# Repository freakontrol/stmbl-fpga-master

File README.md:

DISCLAIMER
===

THE AUTHORS OF THIS SOFTWARE ACCEPT ABSOLUTELY NO LIABILITY FOR
ANY HARM OR LOSS RESULTING FROM ITS USE.  IT IS _EXTREMELY_ UNWISE
TO RELY ON SOFTWARE ALONE FOR SAFETY.  Any machinery capable of
harming persons must have provisions for completely removing power
from all motors, etc, before persons enter any danger area.  All
machinery must be designed to comply with local and national safety
codes, and the authors of this software can not, and do not, take
any responsibility for such compliance.

This firmware in the folder hostmot2-firmware originates from Mesa Electronics.
This repository  is released under the GPLv3.

STMBL FPGA Master
=====

This is a FPGA controller board specifically designed to be used as a master for up to 12 stmbl drives. It can be used for other applications.
The hardware has the same form factor as the [STMBL](https://github.com/freakontrol/stmbl) v5 drives.
The FPGA runs the hostmot2 firmware.

## Hardware overview
- 12 SSerial ports
- 2 SSerial/RS485 ports
- one 26 Pin parallel expansion port (17 IOs)
- one 24V Input
- one 24V Output
- Host connection via Ethernet or SPI (if used with a RPi 4 or 5)
- 24V Power Input (provides also power to the Raspberry Pi)

## Known Bugs

**Please note that the hardware and firmware are in an early prototyping stage.**
Don't manufacture the version 0.9 because of the reversed SSerial pinouts

- affects hardware v0.9: Pinout of SSerial 0-5 and 12-13 is reversed (1-8, 2-7, ...), use a [Rollover cable](https://en.wikipedia.org/wiki/Rollover_cable)
- SSerial 13 ist not working, there seems to be a bug in the PIN file
- At the moment there is no option to enable power to the SSerial ports before loading the hm2 driver. So it is not possible to use SSerial devices that a powered form the SSerial connector. Can be fixed in firmware.

* * * 
If you have questions about this project contact me [here](https://matrix.to/#/@jst:freiburg.social).

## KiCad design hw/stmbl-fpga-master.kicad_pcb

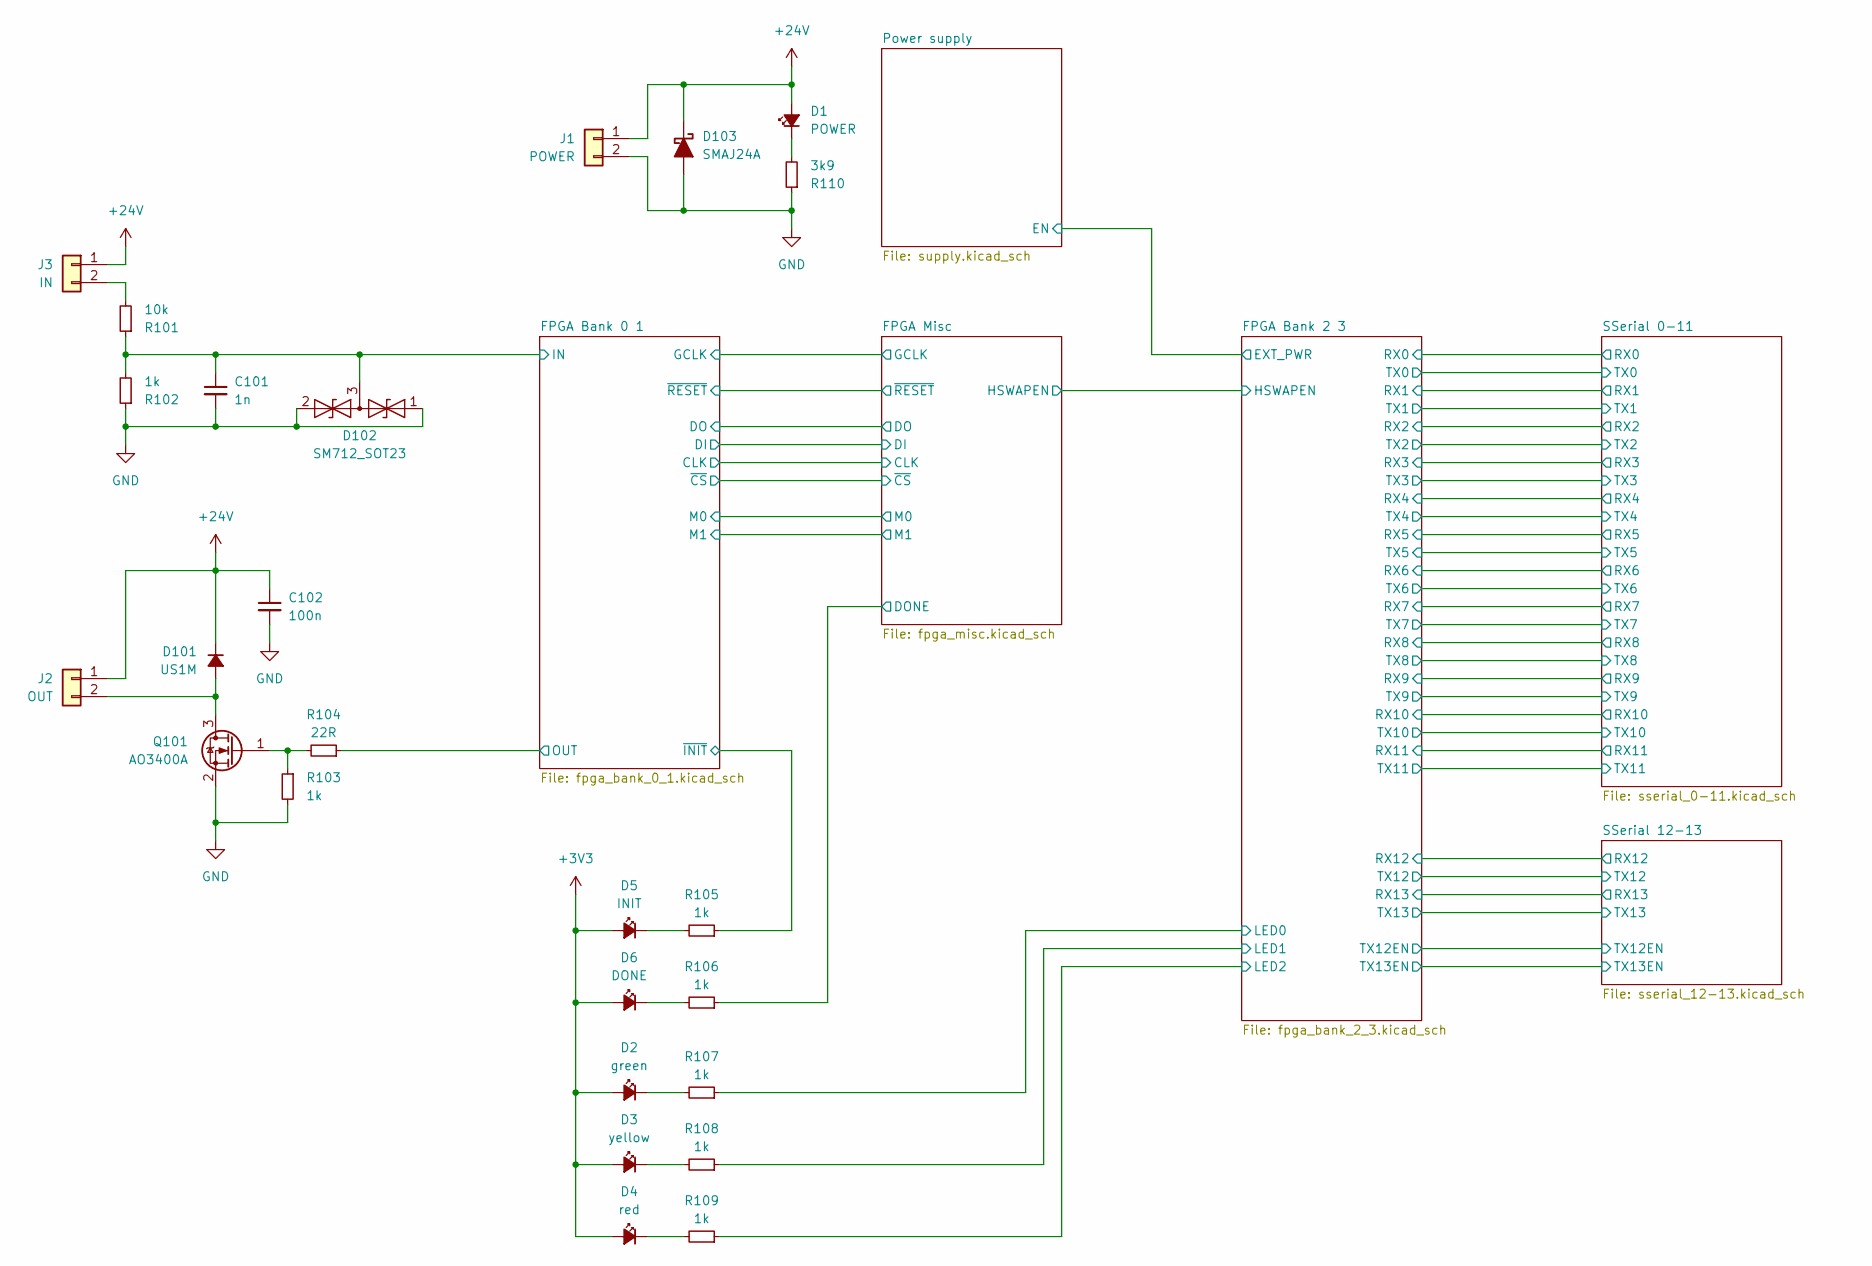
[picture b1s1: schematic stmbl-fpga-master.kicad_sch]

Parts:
C101: 1n; C_0603_1608Metric
C102: 100n; C_0603_1608Metric
D1: POWER; LED-0805-SIDE
D2: green; LED-0805-SIDE
D3: yellow; LED-0805-SIDE
D4: red; LED-0805-SIDE
D5: INIT; LED_0603_1608Metric
D6: DONE; LED_0603_1608Metric
D101: US1M; D_SMA
D102: SM712_SOT23; SOT-23
D103: SMAJ24A; D_SMA
J1: POWER; PhoenixContact_MC_1,5_2-G-3.5_1x02_P3.50mm_Horizontal
J2: OUT; PhoenixContact_MC_1,5_2-G-3.5_1x02_P3.50mm_Horizontal
J3: IN; PhoenixContact_MC_1,5_2-G-3.5_1x02_P3.50mm_Horizontal
Q101: AO3400A; SOT-23
R101: 10k; R_0603_1608Metric
R102, R103, R105, R106, R107, R108, R109: 1k; R_0603_1608Metric
R104: 22R; R_0603_1608Metric
R110: 3k9; R_0603_1608Metric

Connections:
+3V3: D2.2 (A), D3.2 (A), D4.2 (A), D5.2 (A), D6.2 (A); also elsewhere on the board
+24V: C102.1, D1.2 (A), D101.1 (K), D103.1 (K), J1.1, J2.1, J3.1; also elsewhere on the board
/FPGA Bank 0 1/IN: C101.1, D102.3 (common), R101.1, R102.2; also elsewhere on the board
/FPGA Bank 0 1/OUT: R104.1; also elsewhere on the board
/FPGA Bank 0 1/~INIT: R105.1; also elsewhere on the board
/FPGA Bank 2 3/LED0: R107.1; also elsewhere on the board
/FPGA Bank 2 3/LED1: R108.1; also elsewhere on the board
/FPGA Bank 2 3/LED2: R109.1; also elsewhere on the board
/FPGA Misc/DONE: R106.1; also elsewhere on the board
GND: C101.2, C102.2, D102.1 (A1), D102.2 (A2), D103.2 (A), J1.2, Q101.2 (S), R102.1, R103.2, R110.1; also elsewhere on the board
unnamed: D1.1 (K), R110.2
unnamed: D2.1 (K), R107.2
unnamed: D3.1 (K), R108.2
unnamed: D4.1 (K), R109.2
unnamed: D5.1 (K), R105.2
unnamed: D6.1 (K), R106.2
unnamed: D101.2 (A), J2.2, Q101.3 (D)
unnamed: J3.2, R101.2
unnamed: Q101.1 (G), R103.1, R104.2

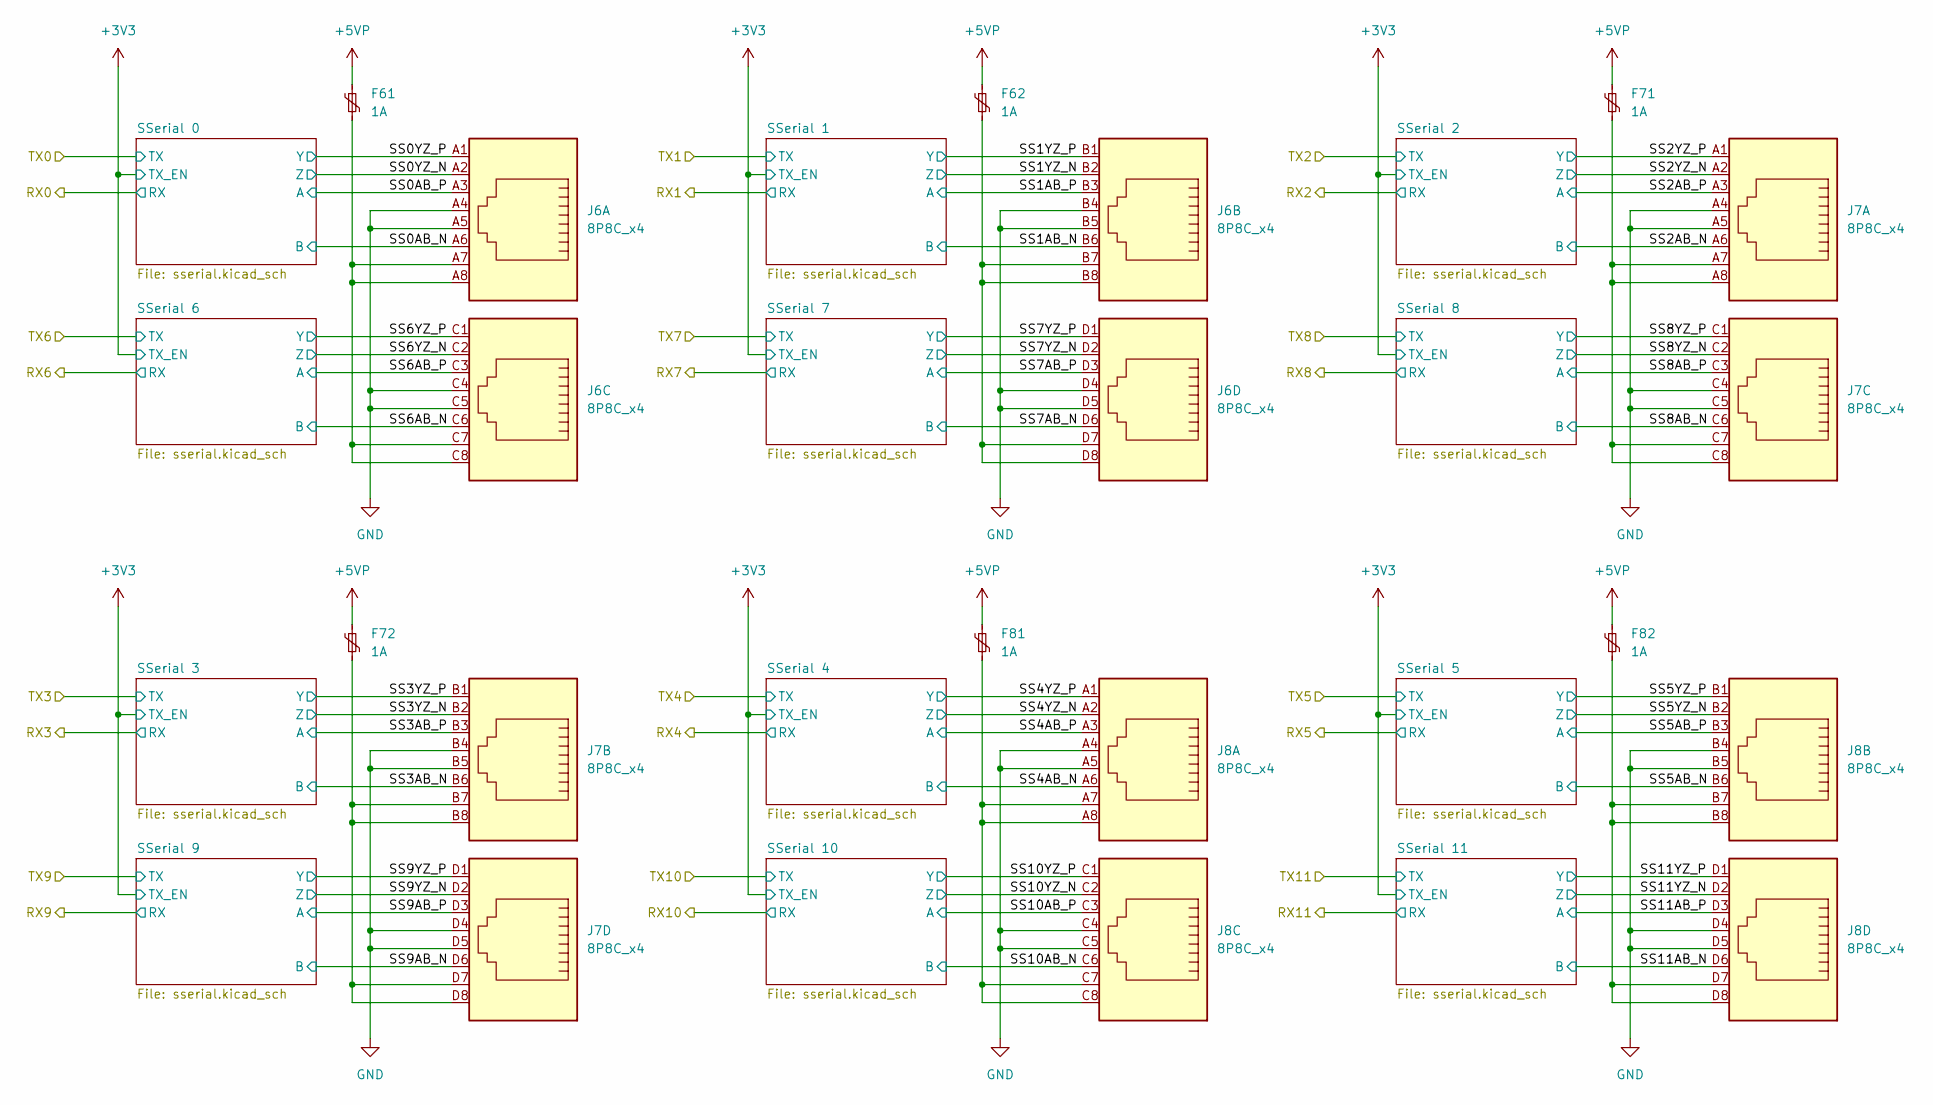
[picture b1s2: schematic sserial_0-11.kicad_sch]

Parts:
F61, F62, F71, F72, F81, F82: 1A; Fuse_1206_3216Metric
J6, J7, J8: 8P8C_x4; MJ5988-B022-HPRN1

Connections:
+5VP: F61.1, F62.1, F71.1, F72.1, F81.1, F82.1; also elsewhere on the board
/SSerial 0-11/SS0AB_N: J6.A6; also elsewhere on the board
/SSerial 0-11/SS0AB_P: J6.A3; also elsewhere on the board
/SSerial 0-11/SS0YZ_N: J6.A2; also elsewhere on the board
/SSerial 0-11/SS0YZ_P: J6.A1; also elsewhere on the board
/SSerial 0-11/SS1AB_N: J6.B6; also elsewhere on the board
/SSerial 0-11/SS1AB_P: J6.B3; also elsewhere on the board
/SSerial 0-11/SS1YZ_N: J6.B2; also elsewhere on the board
/SSerial 0-11/SS1YZ_P: J6.B1; also elsewhere on the board
/SSerial 0-11/SS2AB_N: J7.A6; also elsewhere on the board
/SSerial 0-11/SS2AB_P: J7.A3; also elsewhere on the board
/SSerial 0-11/SS2YZ_N: J7.A2; also elsewhere on the board
/SSerial 0-11/SS2YZ_P: J7.A1; also elsewhere on the board
/SSerial 0-11/SS3AB_N: J7.B6; also elsewhere on the board
/SSerial 0-11/SS3AB_P: J7.B3; also elsewhere on the board
/SSerial 0-11/SS3YZ_N: J7.B2; also elsewhere on the board
/SSerial 0-11/SS3YZ_P: J7.B1; also elsewhere on the board
/SSerial 0-11/SS4AB_N: J8.A6; also elsewhere on the board
/SSerial 0-11/SS4AB_P: J8.A3; also elsewhere on the board
/SSerial 0-11/SS4YZ_N: J8.A2; also elsewhere on the board
/SSerial 0-11/SS4YZ_P: J8.A1; also elsewhere on the board
/SSerial 0-11/SS5AB_N: J8.B6; also elsewhere on the board
/SSerial 0-11/SS5AB_P: J8.B3; also elsewhere on the board
/SSerial 0-11/SS5YZ_N: J8.B2; also elsewhere on the board
/SSerial 0-11/SS5YZ_P: J8.B1; also elsewhere on the board
/SSerial 0-11/SS6AB_N: J6.C6; also elsewhere on the board
/SSerial 0-11/SS6AB_P: J6.C3; also elsewhere on the board
/SSerial 0-11/SS6YZ_N: J6.C2; also elsewhere on the board
/SSerial 0-11/SS6YZ_P: J6.C1; also elsewhere on the board
/SSerial 0-11/SS7AB_N: J6.D6; also elsewhere on the board
/SSerial 0-11/SS7AB_P: J6.D3; also elsewhere on the board
/SSerial 0-11/SS7YZ_N: J6.D2; also elsewhere on the board
/SSerial 0-11/SS7YZ_P: J6.D1; also elsewhere on the board
/SSerial 0-11/SS8AB_N: J7.C6; also elsewhere on the board
/SSerial 0-11/SS8AB_P: J7.C3; also elsewhere on the board
/SSerial 0-11/SS8YZ_N: J7.C2; also elsewhere on the board
/SSerial 0-11/SS8YZ_P: J7.C1; also elsewhere on the board
/SSerial 0-11/SS9AB_N: J7.D6; also elsewhere on the board
/SSerial 0-11/SS9AB_P: J7.D3; also elsewhere on the board
/SSerial 0-11/SS9YZ_N: J7.D2; also elsewhere on the board
/SSerial 0-11/SS9YZ_P: J7.D1; also elsewhere on the board
/SSerial 0-11/SS10AB_N: J8.C6; also elsewhere on the board
/SSerial 0-11/SS10AB_P: J8.C3; also elsewhere on the board
/SSerial 0-11/SS10YZ_N: J8.C2; also elsewhere on the board
/SSerial 0-11/SS10YZ_P: J8.C1; also elsewhere on the board
/SSerial 0-11/SS11AB_N: J8.D6; also elsewhere on the board
/SSerial 0-11/SS11AB_P: J8.D3; also elsewhere on the board
/SSerial 0-11/SS11YZ_N: J8.D2; also elsewhere on the board
/SSerial 0-11/SS11YZ_P: J8.D1; also elsewhere on the board
GND: J6.A4, J6.A5, J6.B4, J6.B5, J6.C4, J6.C5, J6.D4, J6.D5, J7.A4, J7.A5, J7.B4, J7.B5, J7.C4, J7.C5, J7.D4, J7.D5, J8.A4, J8.A5, J8.B4, J8.B5, J8.C4, J8.C5, J8.D4, J8.D5; also elsewhere on the board
unnamed: F61.2, J6.A7, J6.A8, J6.C7, J6.C8
unnamed: F62.2, J6.B7, J6.B8, J6.D7, J6.D8
unnamed: F71.2, J7.A7, J7.A8, J7.C7, J7.C8
unnamed: F72.2, J7.B7, J7.B8, J7.D7, J7.D8
unnamed: F81.2, J8.A7, J8.A8, J8.C7, J8.C8
unnamed: F82.2, J8.B7, J8.B8, J8.D7, J8.D8

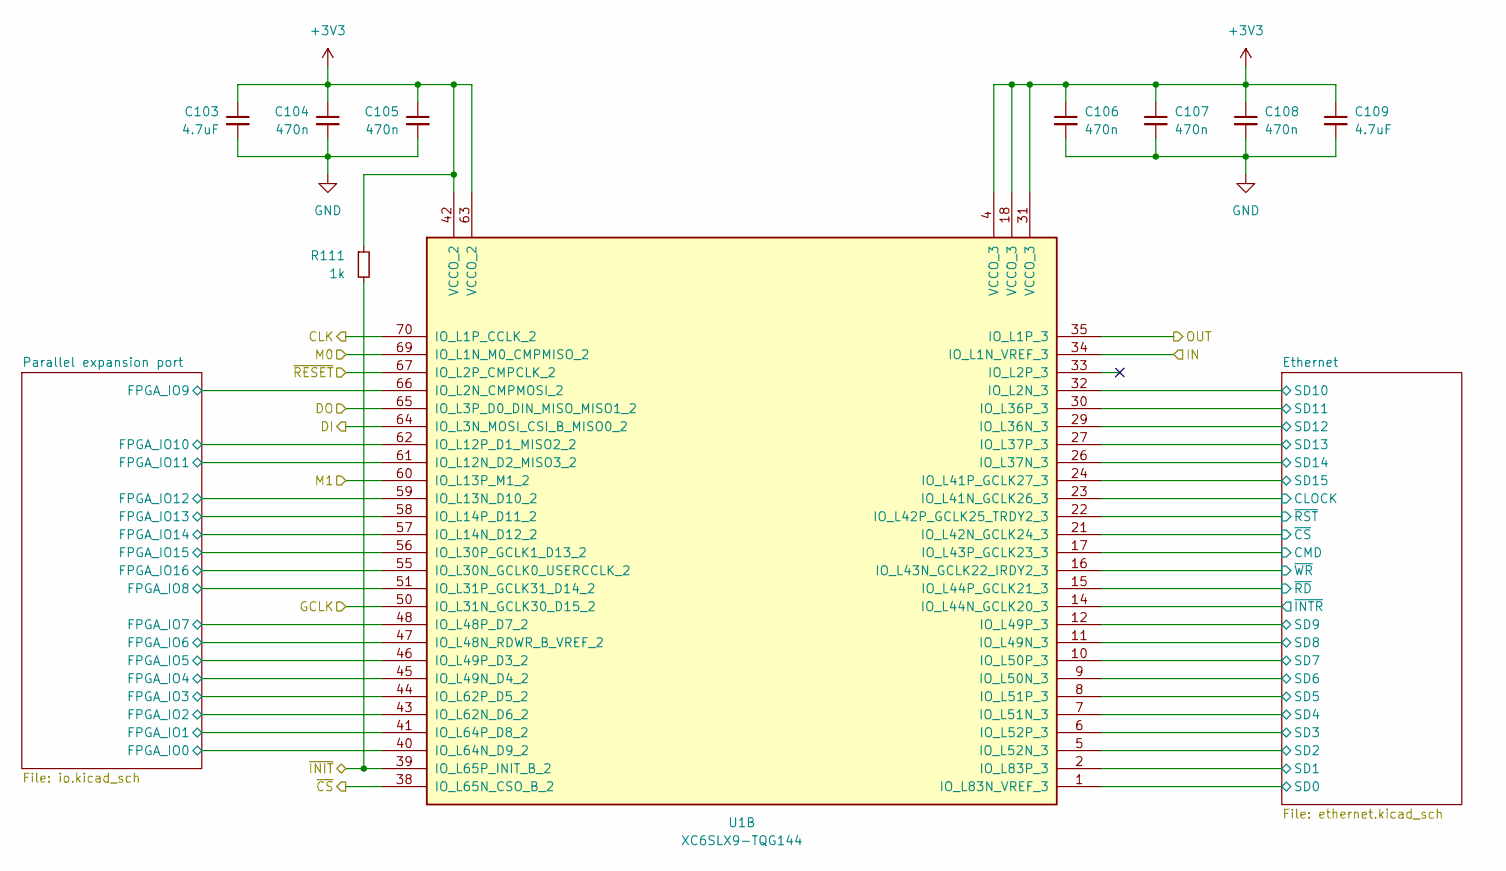
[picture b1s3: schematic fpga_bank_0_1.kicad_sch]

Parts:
C103, C109: 4.7uF; C_0603_1608Metric
C104, C105, C106, C107, C108: 470n; C_0603_1608Metric
R111: 1k; R_0603_1608Metric
U1: XC6SLX9-TQG144; TQFP-144_20x20mm_P0.5mm

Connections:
+3V3: C103.1, C104.1, C105.1, C106.1, C107.1, C108.1, C109.1, R111.1, U1.4 (VCCO_3), U1.18 (VCCO_3), U1.31 (VCCO_3), U1.42 (VCCO_2), U1.63 (VCCO_2); also elsewhere on the board
/FPGA Bank 0 1/CLK: U1.70 (IO_L1P_CCLK_2); also elsewhere on the board
/FPGA Bank 0 1/DI: U1.64 (IO_L3N_MOSI_CSI_B_MISO0_2); also elsewhere on the board
/FPGA Bank 0 1/DO: U1.65 (IO_L3P_D0_DIN_MISO_MISO1_2); also elsewhere on the board
/FPGA Bank 0 1/Ethernet/CLOCK: U1.23 (IO_L41N_GCLK26_3); also elsewhere on the board
/FPGA Bank 0 1/Ethernet/CMD: U1.17 (IO_L43P_GCLK23_3); also elsewhere on the board
/FPGA Bank 0 1/Ethernet/SD0: U1.1 (IO_L83N_VREF_3); also elsewhere on the board
/FPGA Bank 0 1/Ethernet/SD1: U1.2 (IO_L83P_3); also elsewhere on the board
/FPGA Bank 0 1/Ethernet/SD2: U1.5 (IO_L52N_3); also elsewhere on the board
/FPGA Bank 0 1/Ethernet/SD3: U1.6 (IO_L52P_3); also elsewhere on the board
/FPGA Bank 0 1/Ethernet/SD4: U1.7 (IO_L51N_3); also elsewhere on the board
/FPGA Bank 0 1/Ethernet/SD5: U1.8 (IO_L51P_3); also elsewhere on the board
/FPGA Bank 0 1/Ethernet/SD6: U1.9 (IO_L50N_3); also elsewhere on the board
/FPGA Bank 0 1/Ethernet/SD7: U1.10 (IO_L50P_3); also elsewhere on the board
/FPGA Bank 0 1/Ethernet/SD8: U1.11 (IO_L49N_3); also elsewhere on the board
/FPGA Bank 0 1/Ethernet/SD9: U1.12 (IO_L49P_3); also elsewhere on the board
/FPGA Bank 0 1/Ethernet/SD10: U1.32 (IO_L2N_3); also elsewhere on the board
/FPGA Bank 0 1/Ethernet/SD11: U1.30 (IO_L36P_3); also elsewhere on the board
/FPGA Bank 0 1/Ethernet/SD12: U1.29 (IO_L36N_3); also elsewhere on the board
/FPGA Bank 0 1/Ethernet/SD13: U1.27 (IO_L37P_3); also elsewhere on the board
/FPGA Bank 0 1/Ethernet/SD14: U1.26 (IO_L37N_3); also elsewhere on the board
/FPGA Bank 0 1/Ethernet/SD15: U1.24 (IO_L41P_GCLK27_3); also elsewhere on the board
/FPGA Bank 0 1/Ethernet/~CS: U1.21 (IO_L42N_GCLK24_3); also elsewhere on the board
/FPGA Bank 0 1/Ethernet/~INTR: U1.14 (IO_L44N_GCLK20_3); also elsewhere on the board
/FPGA Bank 0 1/Ethernet/~RD: U1.15 (IO_L44P_GCLK21_3); also elsewhere on the board
/FPGA Bank 0 1/Ethernet/~RST: U1.22 (IO_L42P_GCLK25_TRDY2_3); also elsewhere on the board
/FPGA Bank 0 1/Ethernet/~WR: U1.16 (IO_L43N_GCLK22_IRDY2_3); also elsewhere on the board
/FPGA Bank 0 1/GCLK: U1.50 (IO_L31N_GCLK30_D15_2); also elsewhere on the board
/FPGA Bank 0 1/IN: U1.34 (IO_L1N_VREF_3); also elsewhere on the board
/FPGA Bank 0 1/M0: U1.69 (IO_L1N_M0_CMPMISO_2); also elsewhere on the board
/FPGA Bank 0 1/M1: U1.60 (IO_L13P_M1_2); also elsewhere on the board
/FPGA Bank 0 1/OUT: U1.35 (IO_L1P_3); also elsewhere on the board
/FPGA Bank 0 1/Parallel expansion port/FPGA_IO0: U1.40 (IO_L64N_D9_2); also elsewhere on the board
/FPGA Bank 0 1/Parallel expansion port/FPGA_IO1: U1.41 (IO_L64P_D8_2); also elsewhere on the board
/FPGA Bank 0 1/Parallel expansion port/FPGA_IO2: U1.43 (IO_L62N_D6_2); also elsewhere on the board
/FPGA Bank 0 1/Parallel expansion port/FPGA_IO3: U1.44 (IO_L62P_D5_2); also elsewhere on the board
/FPGA Bank 0 1/Parallel expansion port/FPGA_IO4: U1.45 (IO_L49N_D4_2); also elsewhere on the board
/FPGA Bank 0 1/Parallel expansion port/FPGA_IO5: U1.46 (IO_L49P_D3_2); also elsewhere on the board
/FPGA Bank 0 1/Parallel expansion port/FPGA_IO6: U1.47 (IO_L48N_RDWR_B_VREF_2); also elsewhere on the board
/FPGA Bank 0 1/Parallel expansion port/FPGA_IO7: U1.48 (IO_L48P_D7_2); also elsewhere on the board
/FPGA Bank 0 1/Parallel expansion port/FPGA_IO8: U1.51 (IO_L31P_GCLK31_D14_2); also elsewhere on the board
/FPGA Bank 0 1/Parallel expansion port/FPGA_IO9: U1.66 (IO_L2N_CMPMOSI_2); also elsewhere on the board
/FPGA Bank 0 1/Parallel expansion port/FPGA_IO10: U1.62 (IO_L12P_D1_MISO2_2); also elsewhere on the board
/FPGA Bank 0 1/Parallel expansion port/FPGA_IO11: U1.61 (IO_L12N_D2_MISO3_2); also elsewhere on the board
/FPGA Bank 0 1/Parallel expansion port/FPGA_IO12: U1.59 (IO_L13N_D10_2); also elsewhere on the board
/FPGA Bank 0 1/Parallel expansion port/FPGA_IO13: U1.58 (IO_L14P_D11_2); also elsewhere on the board
/FPGA Bank 0 1/Parallel expansion port/FPGA_IO14: U1.57 (IO_L14N_D12_2); also elsewhere on the board
/FPGA Bank 0 1/Parallel expansion port/FPGA_IO15: U1.56 (IO_L30P_GCLK1_D13_2); also elsewhere on the board
/FPGA Bank 0 1/Parallel expansion port/FPGA_IO16: U1.55 (IO_L30N_GCLK0_USERCCLK_2); also elsewhere on the board
/FPGA Bank 0 1/~CS: U1.38 (IO_L65N_CSO_B_2); also elsewhere on the board
/FPGA Bank 0 1/~INIT: R111.2, U1.39 (IO_L65P_INIT_B_2); also elsewhere on the board
/FPGA Bank 0 1/~RESET: U1.67 (IO_L2P_CMPCLK_2); also elsewhere on the board
GND: C103.2, C104.2, C105.2, C106.2, C107.2, C108.2, C109.2; also elsewhere on the board

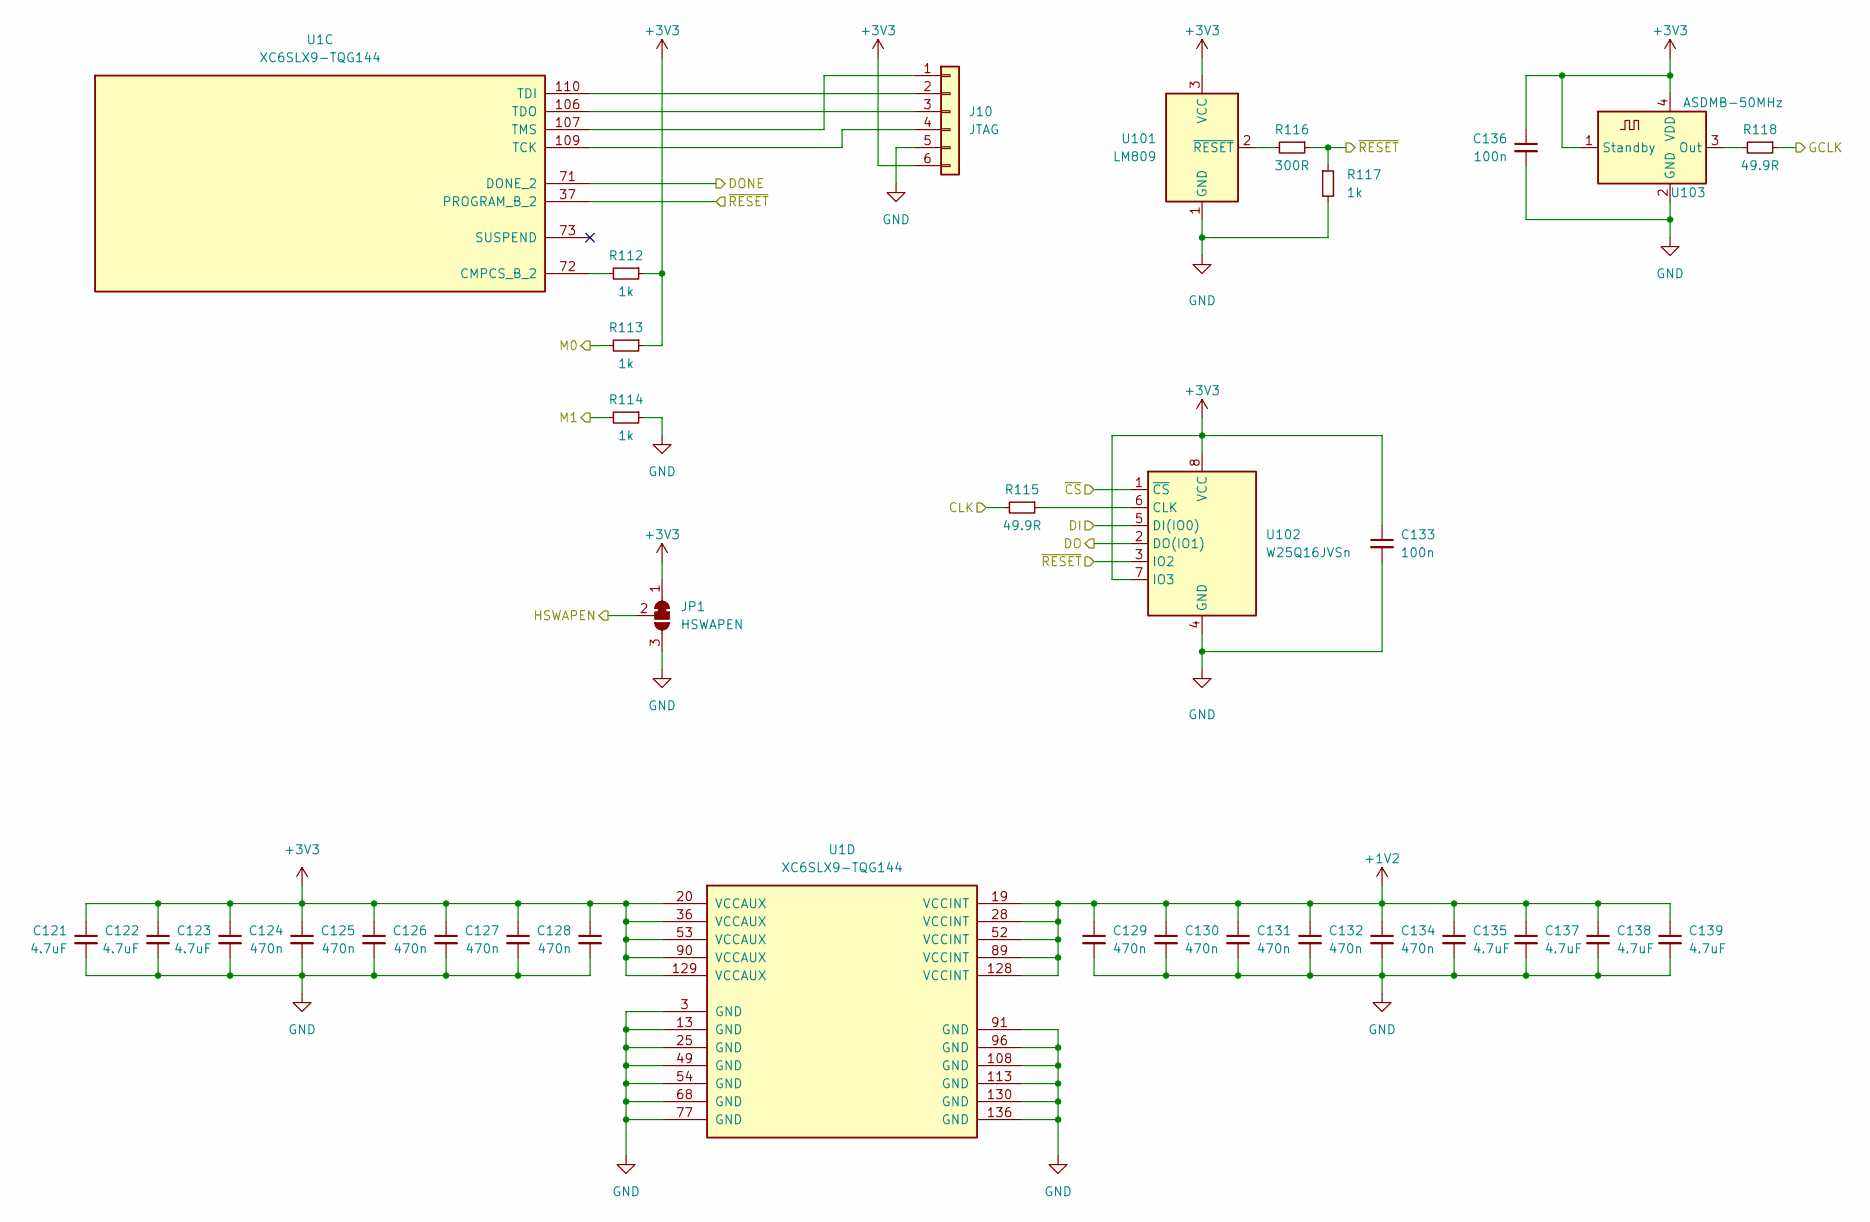
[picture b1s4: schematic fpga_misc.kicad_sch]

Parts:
C121, C122, C123, C135, C137, C138, C139: 4.7uF; C_0603_1608Metric
C124, C125, C126, C127, C128, C129, C130, C131, C132, C134: 470n; C_0603_1608Metric
C133, C136: 100n; C_0603_1608Metric
J10: JTAG; PinHeader_1x06_P2.54mm_Vertical_copy
JP1: HSWAPEN; SolderJumper-3_P1.3mm_Bridged12_RoundedPad1.0x1.5mm
R112, R113, R114, R117: 1k; R_0603_1608Metric
R115, R118: 49.9R; R_0603_1608Metric
R116: 300R; R_0603_1608Metric
U1: XC6SLX9-TQG144; TQFP-144_20x20mm_P0.5mm
U101: LM809; SOT-23
U102: W25Q16JVSn; SOIC-8_3.9x4.9mm_P1.27mm
U103: ASDMB-50MHz; Oscillator_SMD_Abracon_ASDMB-4Pin_2.5x2.0mm

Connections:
+1V2: C129.1, C130.1, C131.1, C132.1, C134.1, C135.1, C137.1, C138.1, C139.1, U1.19 (VCCINT), U1.28 (VCCINT), U1.52 (VCCINT), U1.89 (VCCINT), U1.128 (VCCINT); also elsewhere on the board
+3V3: C121.1, C122.1, C123.1, C124.1, C125.1, C126.1, C127.1, C128.1, C133.1, C136.1, J10.6, JP1.1 (A), R112.1, R113.1, U1.20 (VCCAUX), U1.36 (VCCAUX), U1.53 (VCCAUX), U1.90 (VCCAUX), U1.129 (VCCAUX), U101.3 (VCC), U102.7 (IO3), U102.8 (VCC), U103.1 (Standby), U103.4 (VDD); also elsewhere on the board
/FPGA Bank 0 1/CLK: R115.2; also elsewhere on the board
/FPGA Bank 0 1/DI: U102.5 (DI(IO0)); also elsewhere on the board
/FPGA Bank 0 1/DO: U102.2 (DO(IO1)); also elsewhere on the board
/FPGA Bank 0 1/GCLK: R118.1; also elsewhere on the board
/FPGA Bank 0 1/M0: R113.2; also elsewhere on the board
/FPGA Bank 0 1/M1: R114.2; also elsewhere on the board
/FPGA Bank 0 1/~CS: U102.1 (~CS); also elsewhere on the board
/FPGA Bank 0 1/~RESET: R116.1, R117.1, U1.37 (PROGRAM_B_2), U102.3 (IO2); also elsewhere on the board
/FPGA Bank 2 3/HSWAPEN: JP1.2 (C); also elsewhere on the board
/FPGA Misc/DONE: U1.71 (DONE_2); also elsewhere on the board
GND: C121.2, C122.2, C123.2, C124.2, C125.2, C126.2, C127.2, C128.2, C129.2, C130.2, C131.2, C132.2, C133.2, C134.2, C135.2, C136.2, C137.2, C138.2, C139.2, J10.5, JP1.3 (B), R114.1, R117.2, U1.3 (GND), U1.13 (GND), U1.25 (GND), U1.49 (GND), U1.54 (GND), U1.68 (GND), U1.77 (GND), U1.91 (GND), U1.96 (GND), U1.108 (GND), U1.113 (GND), U1.130 (GND), U1.136 (GND), U101.1 (GND), U102.4 (GND), U103.2 (GND); also elsewhere on the board
unnamed: J10.1, U1.107 (TMS)
unnamed: J10.2, U1.110 (TDI)
unnamed: J10.3, U1.106 (TDO)
unnamed: J10.4, U1.109 (TCK)
unnamed: R112.2, U1.72 (CMPCS_B_2)
unnamed: R116.2, U101.2 (~RESET)
unnamed: R115.1, U102.6 (CLK)
unnamed: R118.2, U103.3 (Out)

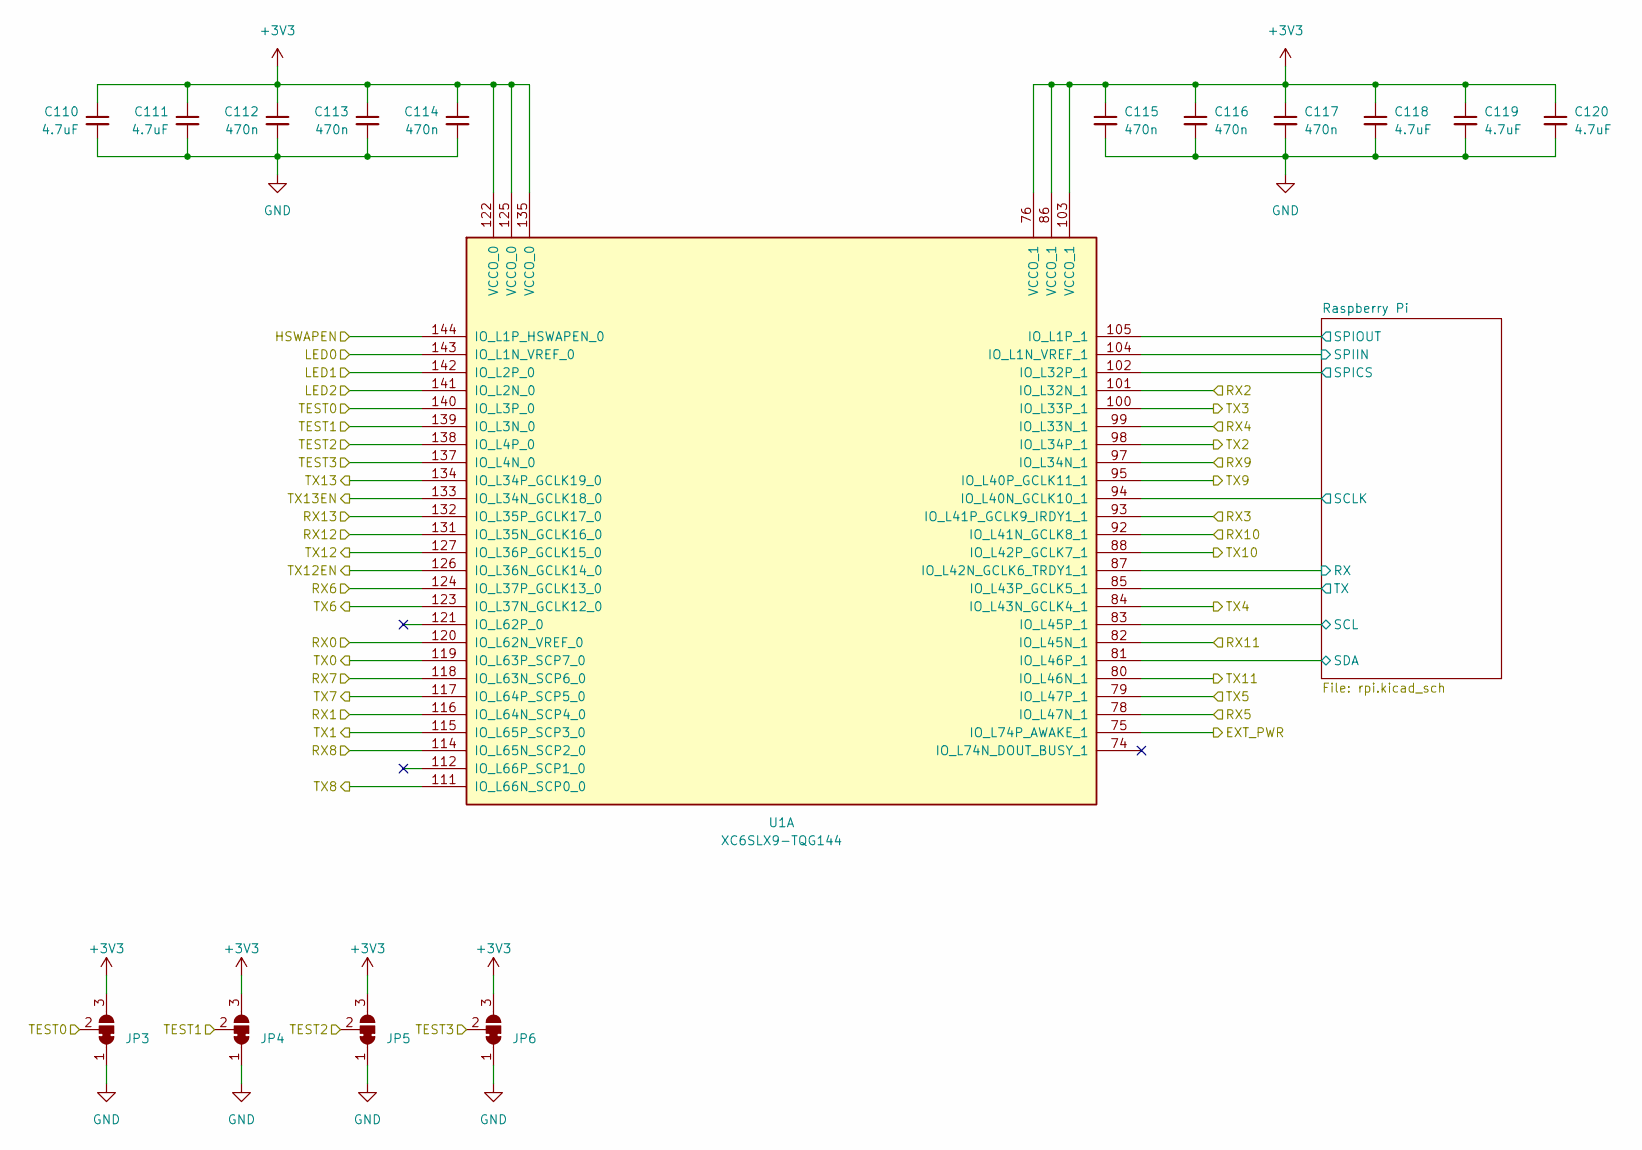
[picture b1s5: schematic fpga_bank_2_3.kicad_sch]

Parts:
C110, C111, C118, C119, C120: 4.7uF; C_0603_1608Metric
C112, C113, C114, C115, C116, C117: 470n; C_0603_1608Metric
JP3, JP4, JP5, JP6: SolderJumper-3_P1.3mm_Open_RoundedPad1.0x1.5mm
U1: XC6SLX9-TQG144; TQFP-144_20x20mm_P0.5mm

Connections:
+3V3: C110.1, C111.1, C112.1, C113.1, C114.1, C115.1, C116.1, C117.1, C118.1, C119.1, C120.1, JP3.3 (B), JP4.3 (B), JP5.3 (B), JP6.3 (B), U1.76 (VCCO_1), U1.86 (VCCO_1), U1.103 (VCCO_1), U1.122 (VCCO_0), U1.125 (VCCO_0), U1.135 (VCCO_0); also elsewhere on the board
/FPGA Bank 2 3/EXT_PWR: U1.75 (IO_L74P_AWAKE_1); also elsewhere on the board
/FPGA Bank 2 3/HSWAPEN: U1.144 (IO_L1P_HSWAPEN_0); also elsewhere on the board
/FPGA Bank 2 3/LED0: U1.143 (IO_L1N_VREF_0); also elsewhere on the board
/FPGA Bank 2 3/LED1: U1.142 (IO_L2P_0); also elsewhere on the board
/FPGA Bank 2 3/LED2: U1.141 (IO_L2N_0); also elsewhere on the board
/FPGA Bank 2 3/RX0: U1.120 (IO_L62N_VREF_0); also elsewhere on the board
/FPGA Bank 2 3/RX1: U1.116 (IO_L64N_SCP4_0); also elsewhere on the board
/FPGA Bank 2 3/RX2: U1.101 (IO_L32N_1); also elsewhere on the board
/FPGA Bank 2 3/RX3: U1.93 (IO_L41P_GCLK9_IRDY1_1); also elsewhere on the board
/FPGA Bank 2 3/RX4: U1.99 (IO_L33N_1); also elsewhere on the board
/FPGA Bank 2 3/RX5: U1.78 (IO_L47N_1); also elsewhere on the board
/FPGA Bank 2 3/RX6: U1.124 (IO_L37P_GCLK13_0); also elsewhere on the board
/FPGA Bank 2 3/RX7: U1.118 (IO_L63N_SCP6_0); also elsewhere on the board
/FPGA Bank 2 3/RX8: U1.114 (IO_L65N_SCP2_0); also elsewhere on the board
/FPGA Bank 2 3/RX9: U1.97 (IO_L34N_1); also elsewhere on the board
/FPGA Bank 2 3/RX10: U1.92 (IO_L41N_GCLK8_1); also elsewhere on the board
/FPGA Bank 2 3/RX11: U1.82 (IO_L45N_1); also elsewhere on the board
/FPGA Bank 2 3/RX12: U1.131 (IO_L35N_GCLK16_0); also elsewhere on the board
/FPGA Bank 2 3/RX13: U1.132 (IO_L35P_GCLK17_0); also elsewhere on the board
/FPGA Bank 2 3/Raspberry Pi/RX: U1.87 (IO_L42N_GCLK6_TRDY1_1); also elsewhere on the board
/FPGA Bank 2 3/Raspberry Pi/SCL: U1.83 (IO_L45P_1); also elsewhere on the board
/FPGA Bank 2 3/Raspberry Pi/SCLK: U1.94 (IO_L40N_GCLK10_1); also elsewhere on the board
/FPGA Bank 2 3/Raspberry Pi/SDA: U1.81 (IO_L46P_1); also elsewhere on the board
/FPGA Bank 2 3/Raspberry Pi/SPICS: U1.102 (IO_L32P_1); also elsewhere on the board
/FPGA Bank 2 3/Raspberry Pi/SPIIN: U1.104 (IO_L1N_VREF_1); also elsewhere on the board
/FPGA Bank 2 3/Raspberry Pi/SPIOUT: U1.105 (IO_L1P_1); also elsewhere on the board
/FPGA Bank 2 3/Raspberry Pi/TX: U1.85 (IO_L43P_GCLK5_1); also elsewhere on the board
/FPGA Bank 2 3/TEST0: JP3.2 (C), U1.140 (IO_L3P_0); also elsewhere on the board
/FPGA Bank 2 3/TEST1: JP4.2 (C), U1.139 (IO_L3N_0); also elsewhere on the board
/FPGA Bank 2 3/TEST2: JP5.2 (C), U1.138 (IO_L4P_0); also elsewhere on the board
/FPGA Bank 2 3/TEST3: JP6.2 (C), U1.137 (IO_L4N_0); also elsewhere on the board
/FPGA Bank 2 3/TX0: U1.119 (IO_L63P_SCP7_0); also elsewhere on the board
/FPGA Bank 2 3/TX1: U1.115 (IO_L65P_SCP3_0); also elsewhere on the board
/FPGA Bank 2 3/TX2: U1.98 (IO_L34P_1); also elsewhere on the board
/FPGA Bank 2 3/TX3: U1.100 (IO_L33P_1); also elsewhere on the board
/FPGA Bank 2 3/TX4: U1.84 (IO_L43N_GCLK4_1); also elsewhere on the board
/FPGA Bank 2 3/TX5: U1.79 (IO_L47P_1); also elsewhere on the board
/FPGA Bank 2 3/TX6: U1.123 (IO_L37N_GCLK12_0); also elsewhere on the board
/FPGA Bank 2 3/TX7: U1.117 (IO_L64P_SCP5_0); also elsewhere on the board
/FPGA Bank 2 3/TX8: U1.111 (IO_L66N_SCP0_0); also elsewhere on the board
/FPGA Bank 2 3/TX9: U1.95 (IO_L40P_GCLK11_1); also elsewhere on the board
/FPGA Bank 2 3/TX10: U1.88 (IO_L42P_GCLK7_1); also elsewhere on the board
/FPGA Bank 2 3/TX11: U1.80 (IO_L46N_1); also elsewhere on the board
/FPGA Bank 2 3/TX12: U1.127 (IO_L36P_GCLK15_0); also elsewhere on the board
/FPGA Bank 2 3/TX12EN: U1.126 (IO_L36N_GCLK14_0); also elsewhere on the board
/FPGA Bank 2 3/TX13: U1.134 (IO_L34P_GCLK19_0); also elsewhere on the board
/FPGA Bank 2 3/TX13EN: U1.133 (IO_L34N_GCLK18_0); also elsewhere on the board
GND: C110.2, C111.2, C112.2, C113.2, C114.2, C115.2, C116.2, C117.2, C118.2, C119.2, C120.2, JP3.1 (A), JP4.1 (A), JP5.1 (A), JP6.1 (A); also elsewhere on the board

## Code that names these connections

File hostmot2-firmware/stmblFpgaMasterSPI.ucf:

NET "CLK" TNM_NET = "CLK";
TIMESPEC "TS_CLK" = PERIOD "CLK" 19.9 ns HIGH 50 %;

NET "COM_SPICLK" TNM_NET = "COM_SPICLK";
TIMESPEC "TS_COM_SPICLK" = PERIOD "COM_SPICLK" 10 ns HIGH 50 %;

NET	"RECONFIG"	LOC ="P67"	 | IOSTANDARD = LVTTL | DRIVE = 4 | SLEW = SLOW ;
NET	"SPICS"		LOC ="P38"	 | IOSTANDARD = LVTTL | DRIVE = 4 | SLEW = SLOW ;
NET	"SPIIN"		LOC ="P65"	 | IOSTANDARD = LVTTL ;
NET	"SPIOUT"	LOC ="P64"	 | IOSTANDARD = LVTTL | DRIVE = 4 | SLEW = SLOW ;
NET	"SPICLK"	LOC ="P70"	 | IOSTANDARD = LVTTL | DRIVE = 4 | SLEW = SLOW ;
NET	"NINIT"		LOC ="P39"	 | IOSTANDARD = LVTTL | DRIVE = 12 | SLEW = SLOW ; 
NET	"CLK"		LOC ="P50"	 | IOSTANDARD = LVTTL | DRIVE = 4 | SLEW = SLOW ;
NET	"TEST0"	    LOC ="P74"	 | IOSTANDARD = LVTTL;

########## LED ##########
NET	"LEDS<0>"	LOC ="P143"	 | IOSTANDARD = LVTTL | DRIVE = 8 | SLEW = SLOW ;
NET	"LEDS<1>"	LOC ="P142"	 | IOSTANDARD = LVTTL | DRIVE = 8 | SLEW = SLOW ;
NET	"LEDS<2>"	LOC ="P141"	 | IOSTANDARD = LVTTL | DRIVE = 8 | SLEW = SLOW ;
NET	"LEDS<3>"	LOC ="P140"	 | IOSTANDARD = LVTTL | DRIVE = 8 | SLEW = SLOW ;   # nc

########## SPI host ##########
NET	"COM_SPICLK"    LOC ="P94"	 | IOSTANDARD = LVTTL;		                        # RPIO11
NET	"COM_SPIIN"	    LOC ="P105"	 | IOSTANDARD = LVTTL;			                    # RPIO10
NET	"COM_SPIOUT"	LOC ="P104"	 | IOSTANDARD = LVTTL | DRIVE = 4 | SLEW = FAST ;	# RPIO9
NET	"COM_SPICS"	    LOC ="P102"	 | IOSTANDARD = LVTTL; 			                    # RPIO8

########## parallel expansion port ##########
NET	"IOBITS<0>"     LOC ="P40"	 | IOSTANDARD = LVTTL | DRIVE = 24 | SLEW = SLOW ;
NET	"IOBITS<1>"	    LOC ="P41"	 | IOSTANDARD = LVTTL | DRIVE = 24 | SLEW = SLOW ;
NET	"IOBITS<2>"	    LOC ="P43"	 | IOSTANDARD = LVTTL | DRIVE = 24 | SLEW = SLOW ;
NET	"IOBITS<3>"	    LOC ="P44"	 | IOSTANDARD = LVTTL | DRIVE = 24 | SLEW = SLOW ;
NET	"IOBITS<4>"	    LOC ="P45"	 | IOSTANDARD = LVTTL | DRIVE = 24 | SLEW = SLOW ;
NET	"IOBITS<5>"	    LOC ="P46"	 | IOSTANDARD = LVTTL | DRIVE = 24 | SLEW = SLOW ;
NET	"IOBITS<6>"	    LOC ="P47"	 | IOSTANDARD = LVTTL | DRIVE = 24 | SLEW = SLOW ;
NET	"IOBITS<7>"	    LOC ="P48"	 | IOSTANDARD = LVTTL | DRIVE = 24 | SLEW = SLOW ;
NET	"IOBITS<8>"	    LOC ="P51"	 | IOSTANDARD = LVTTL | DRIVE = 24 | SLEW = SLOW ;
NET	"IOBITS<9>"	    LOC ="P66"	 | IOSTANDARD = LVTTL | DRIVE = 24 | SLEW = SLOW ;
NET	"IOBITS<10>"	LOC ="P62"	 | IOSTANDARD = LVTTL | DRIVE = 24 | SLEW = SLOW ;
NET	"IOBITS<11>"	LOC ="P61"	 | IOSTANDARD = LVTTL | DRIVE = 24 | SLEW = SLOW ;
NET	"IOBITS<12>"	LOC ="P59"	 | IOSTANDARD = LVTTL | DRIVE = 24 | SLEW = SLOW ;
NET	"IOBITS<13>"	LOC ="P58"	 | IOSTANDARD = LVTTL | DRIVE = 24 | SLEW = SLOW ;
NET	"IOBITS<14>"	LOC ="P57"	 | IOSTANDARD = LVTTL | DRIVE = 24 | SLEW = SLOW ;
NET	"IOBITS<15>"	LOC ="P56"	 | IOSTANDARD = LVTTL | DRIVE = 24 | SLEW = SLOW ;
NET	"IOBITS<16>"	LOC ="P55"	 | IOSTANDARD = LVTTL | DRIVE = 24 | SLEW = SLOW ;

########## SSerial ##########
NET	"IOBITS<17>"	LOC ="P120"	 | IOSTANDARD = LVTTL | DRIVE = 24 | SLEW = SLOW ;
NET	"IOBITS<18>"	LOC ="P119"	 | IOSTANDARD = LVTTL | DRIVE = 24 | SLEW = SLOW ;
NET	"IOBITS<19>"	LOC ="P116"	 | IOSTANDARD = LVTTL | DRIVE = 24 | SLEW = SLOW ;
NET	"IOBITS<20>"	LOC ="P115"	 | IOSTANDARD = LVTTL | DRIVE = 24 | SLEW = SLOW ;
NET	"IOBITS<21>"	LOC ="P101"	 | IOSTANDARD = LVTTL | DRIVE = 24 | SLEW = SLOW ;
NET	"IOBITS<22>"	LOC ="P98"	 | IOSTANDARD = LVTTL | DRIVE = 24 | SLEW = SLOW ;
NET	"IOBITS<23>"	LOC ="P93"	 | IOSTANDARD = LVTTL | DRIVE = 24 | SLEW = SLOW ;
NET	"IOBITS<24>"	LOC ="P100"	 | IOSTANDARD = LVTTL | DRIVE = 24 | SLEW = SLOW ;
NET	"IOBITS<25>"	LOC ="P99"	 | IOSTANDARD = LVTTL | DRIVE = 24 | SLEW = SLOW ;
NET	"IOBITS<26>"	LOC ="P84"	 | IOSTANDARD = LVTTL | DRIVE = 24 | SLEW = SLOW ;
NET	"IOBITS<27>"	LOC ="P78"	 | IOSTANDARD = LVTTL | DRIVE = 24 | SLEW = SLOW ;
NET	"IOBITS<28>"	LOC ="P79"	 | IOSTANDARD = LVTTL | DRIVE = 24 | SLEW = SLOW ;
NET	"IOBITS<29>"	LOC ="P124"	 | IOSTANDARD = LVTTL | DRIVE = 24 | SLEW = SLOW ;
NET	"IOBITS<30>"	LOC ="P123"	 | IOSTANDARD = LVTTL | DRIVE = 24 | SLEW = SLOW ;
NET	"IOBITS<31>"	LOC ="P118"	 | IOSTANDARD = LVTTL | DRIVE = 24 | SLEW = SLOW ;
NET	"IOBITS<32>"	LOC ="P117"	 | IOSTANDARD = LVTTL | DRIVE = 24 | SLEW = SLOW ;
NET	"IOBITS<33>"	LOC ="P114"	 | IOSTANDARD = LVTTL | DRIVE = 24 | SLEW = SLOW ;
NET	"IOBITS<34>"	LOC ="P111"	 | IOSTANDARD = LVTTL | DRIVE = 24 | SLEW = SLOW ;
NET	"IOBITS<35>"	LOC ="P97"	 | IOSTANDARD = LVTTL | DRIVE = 24 | SLEW = SLOW ;
NET	"IOBITS<36>"	LOC ="P95"	 | IOSTANDARD = LVTTL | DRIVE = 24 | SLEW = SLOW ;
NET	"IOBITS<37>"	LOC ="P92"	 | IOSTANDARD = LVTTL | DRIVE = 24 | SLEW = SLOW ;
NET	"IOBITS<38>"	LOC ="P88"	 | IOSTANDARD = LVTTL | DRIVE = 24 | SLEW = SLOW ;
NET	"IOBITS<39>"	LOC ="P82"	 | IOSTANDARD = LVTTL | DRIVE = 24 | SLEW = SLOW ;
NET	"IOBITS<40>"	LOC ="P80"	 | IOSTANDARD = LVTTL | DRIVE = 24 | SLEW = SLOW ;
NET	"IOBITS<41>"	LOC ="P131"	 | IOSTANDARD = LVTTL | DRIVE = 24 | SLEW = SLOW ;
NET	"IOBITS<42>"	LOC ="P127"	 | IOSTANDARD = LVTTL | DRIVE = 24 | SLEW = SLOW ;
NET	"IOBITS<45>"	LOC ="P126"	 | IOSTANDARD = LVTTL | DRIVE = 24 | SLEW = SLOW ;  # tx en
NET	"IOBITS<43>"	LOC ="P132"	 | IOSTANDARD = LVTTL | DRIVE = 24 | SLEW = SLOW ;
NET	"IOBITS<44>"	LOC ="P134"	 | IOSTANDARD = LVTTL | DRIVE = 24 | SLEW = SLOW ;
NET	"IOBITS<46>"	LOC ="P133"	 | IOSTANDARD = LVTTL | DRIVE = 24 | SLEW = SLOW ;  # tx en
NET	"IOBITS<47>"	LOC ="P75"	 | IOSTANDARD = LVTTL | DRIVE = 24 | SLEW = SLOW ;  # ext pwr en
